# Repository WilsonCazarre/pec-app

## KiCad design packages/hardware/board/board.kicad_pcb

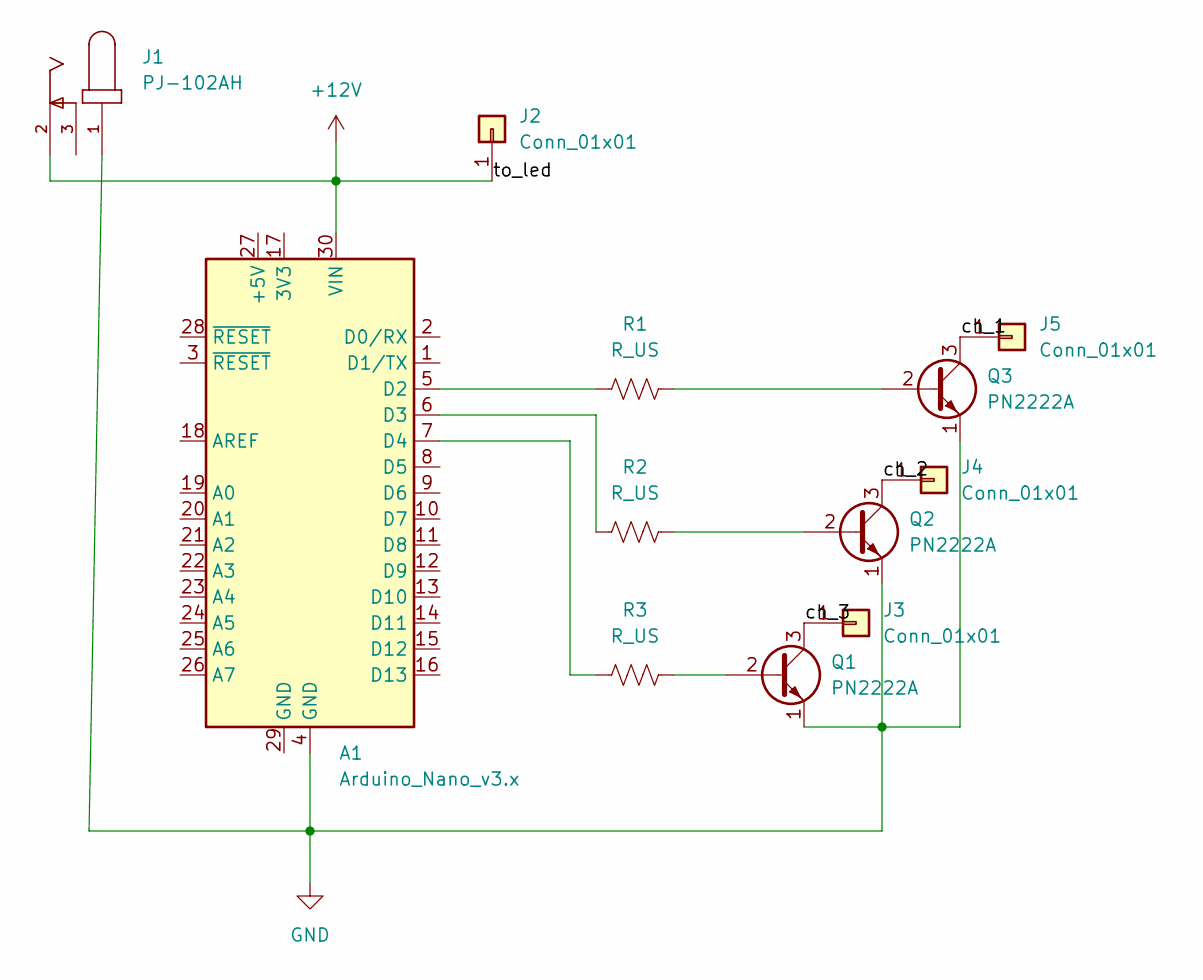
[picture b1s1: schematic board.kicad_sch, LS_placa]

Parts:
A1: Arduino_Nano_v3.x; Arduino_Nano
J1: PJ-102AH; CUI_PJ-102AH; PART_REV 1.02
J2, J3, J4, J5: Conn_01x01; Pin_D0.7mm_L6.5mm_W1.8mm_FlatFork
Q1, Q2, Q3: PN2222A; TO-92_Inline
R1, R2, R3: R_US; R_Axial_DIN0204_L3.6mm_D1.6mm_P2.54mm_Vertical

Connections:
+12V: A1.30 (VIN), J1.2, J2.1
/ch_1: J5.1, Q3.3 (C)
/ch_2: J4.1, Q2.3 (C)
/ch_3: J3.1, Q1.3 (C)
GND: A1.4 (GND), J1.1, Q1.1 (E), Q2.1 (E), Q3.1 (E)
unnamed: Q1.2 (B), R3.2
unnamed: Q2.2 (B), R2.2
unnamed: Q3.2 (B), R1.2
unnamed: A1.5 (D2), R1.1
unnamed: A1.6 (D3), R2.1
unnamed: A1.7 (D4), R3.1

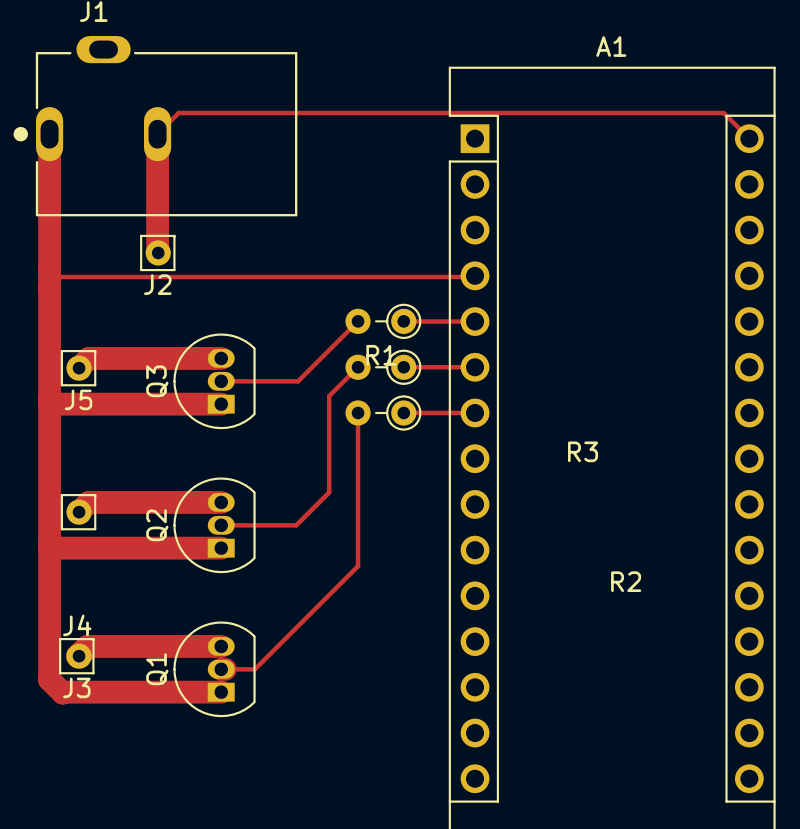
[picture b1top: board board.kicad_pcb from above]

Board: 2 copper layers, 12 parts (0 on the bottom side), 11 nets.

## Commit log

2022-04-25 Inital Commit
2022-04-25 update requirement
2022-04-30 adicionado o decodificador do arduino
2022-05-08 com autofinder
2022-05-09 terminei o COM autofinder
2022-05-09 funções de setup e estáticas terminadas
2022-05-16 inicio das funções temporizadas
2022-05-23 testando as funções
2022-06-06 back end finalizado
2022-06-06 iniciando o dev da pcb
2022-06-20 initial desktop project
2022-08-12 final app version
